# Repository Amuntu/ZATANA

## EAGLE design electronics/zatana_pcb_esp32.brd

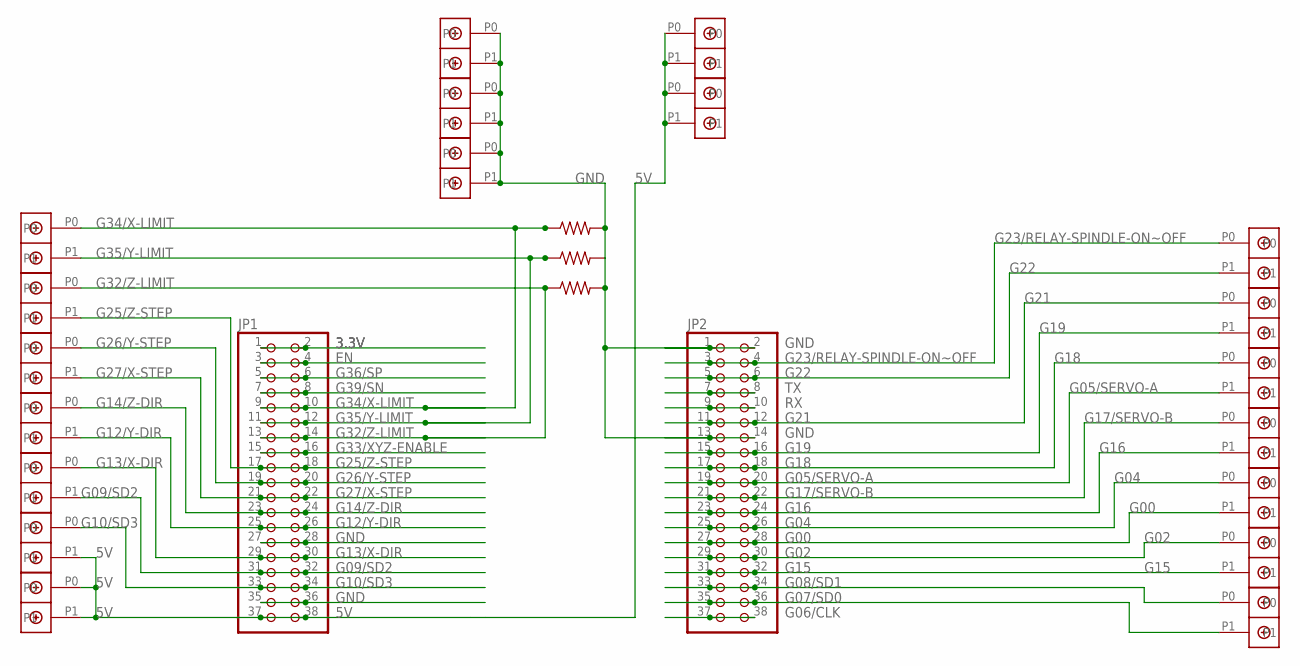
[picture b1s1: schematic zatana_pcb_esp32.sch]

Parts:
JP1, JP2: PINHD-2X19_2.54-90°; 2X19/90
R1, R2, R3: R-US_0207/10; 0207/10
U$2, U$3, U$4, U$5, U$6, U$7, U$8, U$9, U$10, U$11, U$12, U$13, U$14, U$15, U$16, U$18, U$19, U$20, U$21: DBCONN-1X2

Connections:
3.3V: JP1.1, JP1.2
5V: JP1.37, JP1.38, U$7.P1, U$8.P0, U$8.P1, U$18.P0, U$18.P1, U$19.P0, U$19.P1
EN: JP1.3, JP1.4
G00: JP2.27, JP2.28, U$11.P1
G02: JP2.29, JP2.30, U$12.P0
G04: JP2.25, JP2.26, U$11.P0
G05/SERVO-A: JP2.19, JP2.20, U$9.P1
G06/CLK: JP2.37, JP2.38
G07/SD0: JP2.35, JP2.36, U$13.P1
G08/SD1: JP2.33, JP2.34, U$13.P0
G09/SD2: JP1.31, JP1.32, U$6.P1
G10/SD3: JP1.33, JP1.34, U$7.P0
G12/Y-DIR: JP1.25, JP1.26, U$5.P1
G13/X-DIR: JP1.29, JP1.30, U$6.P0
G14/Z-DIR: JP1.23, JP1.24, U$5.P0
G15: JP2.31, JP2.32, U$12.P1
G16: JP2.23, JP2.24, U$10.P1
G17/SERVO-B: JP2.21, JP2.22, U$10.P0
G18: JP2.17, JP2.18, U$9.P0
G19: JP2.15, JP2.16, U$20.P1
G21: JP2.11, JP2.12, U$20.P0
G22: JP2.5, JP2.6, U$21.P1
G23/RELAY-SPINDLE-ON~OFF: JP2.3, JP2.4, U$21.P0
G25/Z-STEP: JP1.17, JP1.18, U$2.P1
G26/Y-STEP: JP1.19, JP1.20, U$4.P0
G27/X-STEP: JP1.21, JP1.22, U$4.P1
G32/Z-LIMIT: JP1.13, JP1.14, R3.1, U$2.P0
G33/XYZ-ENABLE: JP1.15, JP1.16
G34/X-LIMIT: JP1.9, JP1.10, R1.1, U$3.P0
G35/Y-LIMIT: JP1.11, JP1.12, R2.1, U$3.P1
G36/SP: JP1.5, JP1.6
G39/SN: JP1.7, JP1.8
GND: JP1.27, JP1.28, JP1.35, JP1.36, JP2.1, JP2.2, JP2.13, JP2.14, R1.2, R2.2, R3.2, U$14.P0, U$14.P1, U$15.P0, U$15.P1, U$16.P0, U$16.P1
RX: JP2.9, JP2.10
TX: JP2.7, JP2.8

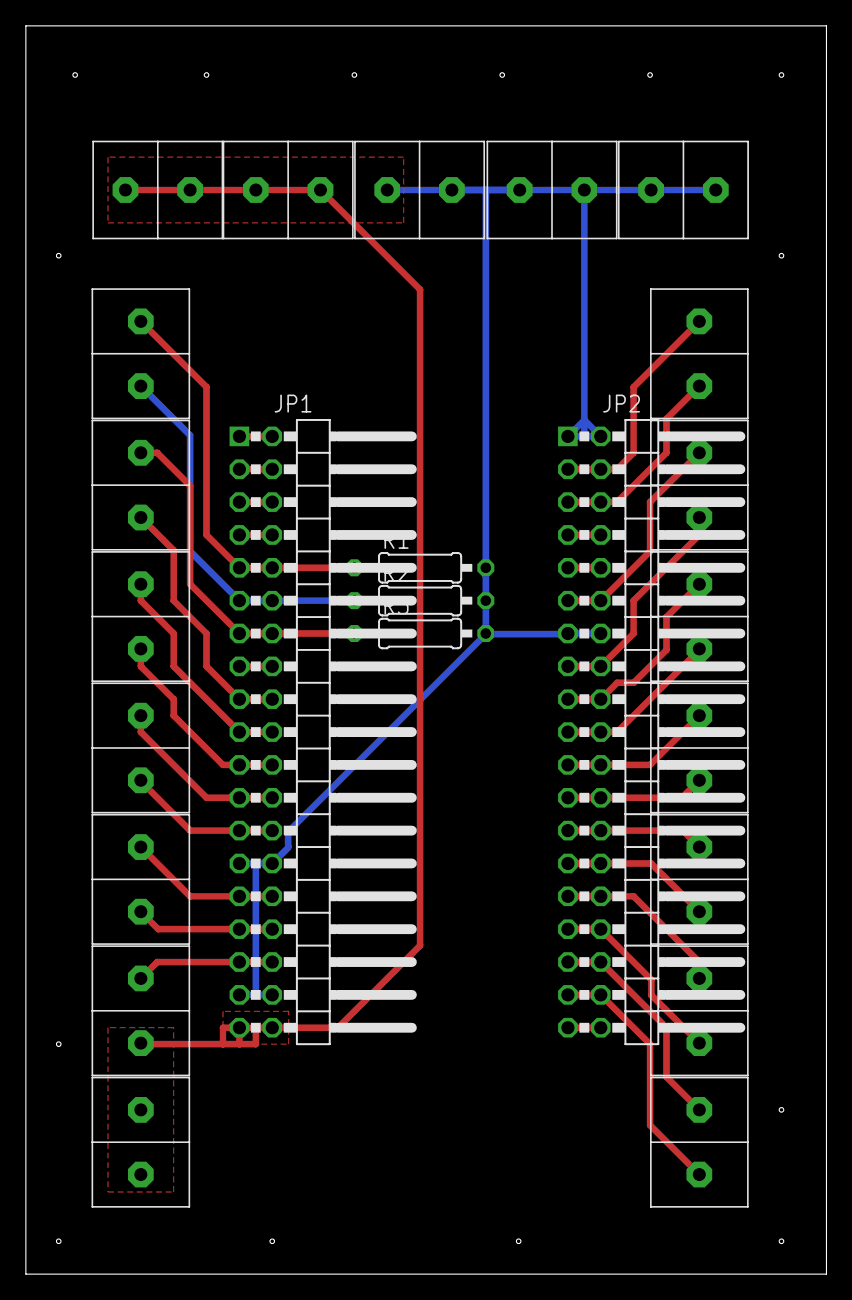
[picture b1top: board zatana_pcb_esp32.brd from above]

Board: 2 copper layers, 61.9 x 96.5 mm, 24 parts (0 on the bottom side), 35 nets.
